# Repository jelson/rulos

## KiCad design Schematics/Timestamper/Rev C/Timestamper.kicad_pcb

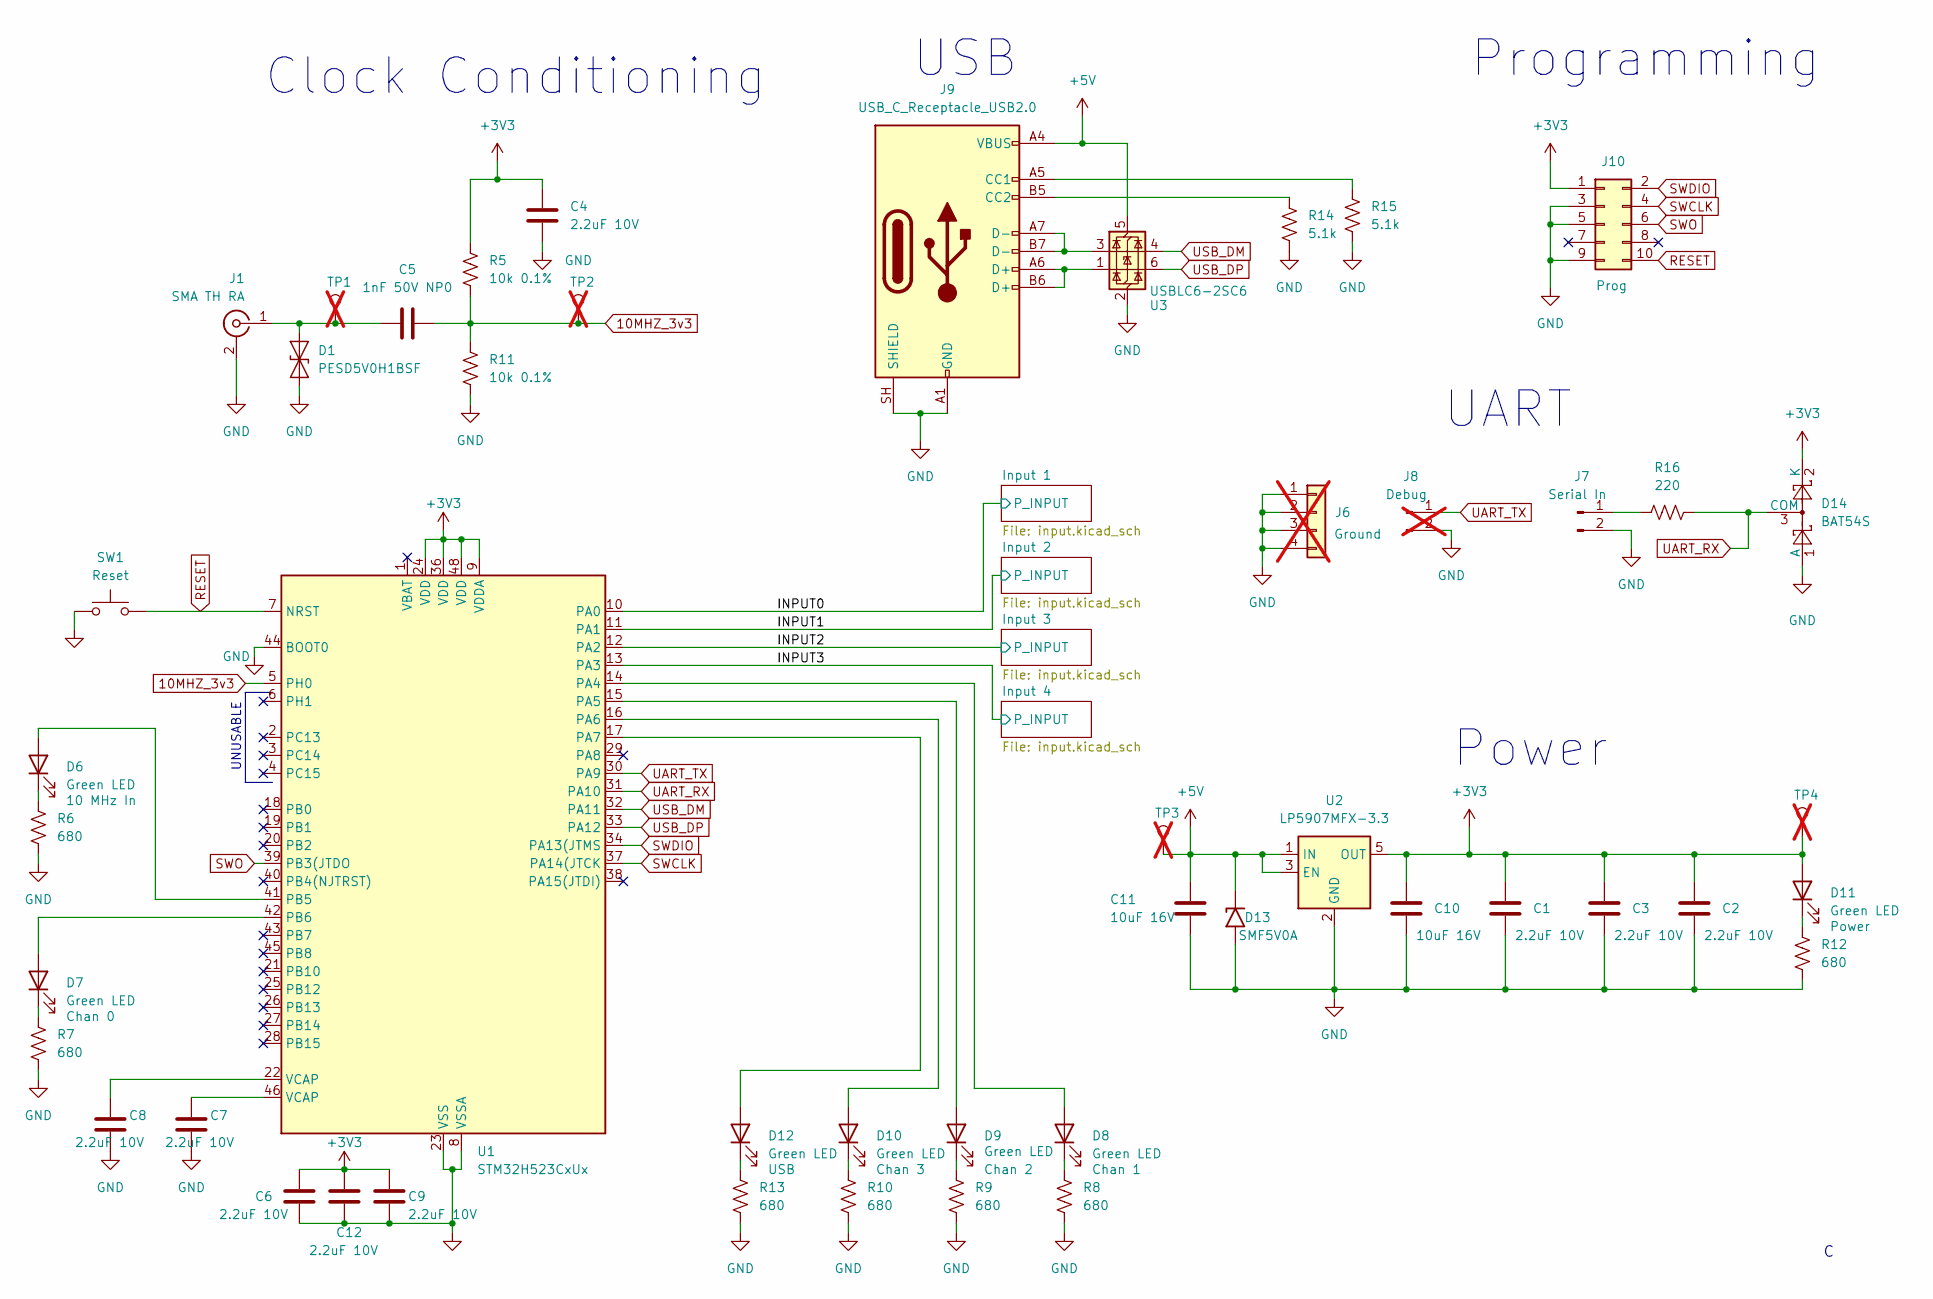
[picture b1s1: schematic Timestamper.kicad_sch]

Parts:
C1, C2, C3, C4, C6, C7, C8, C9, C12: 2.2uF 10V; C_0603_1608Metric_Pad1.08x0.95mm_HandSolder
C5: 1nF 50V NP0; C_0603_1608Metric_Pad1.08x0.95mm_HandSolder
C10, C11: 10uF 16V; C_0805_2012Metric_Pad1.18x1.45mm_HandSolder
D1: PESD5V0H1BSF; Nexperia_DSN0603-2_0.6x0.3mm_P0.4mm
D6, D7, D8, D9, D10, D11, D12: Green LED; LED_0603_1608Metric_Pad1.05x0.95mm_HandSolder
D13: SMF5V0A; D_SOD-123F
D14: BAT54S; SOT-23
J1: SMA TH RA; LINX_CONSMA002-G
J6: 0.1" Header; PinHeader_1x04_P2.54mm_Vertical; not fitted
J7: 0.1" Header; PinHeader_1x02_P2.54mm_Vertical
J8: 0.1" Header; PinHeader_1x02_P2.54mm_Vertical; not fitted
J9: USB_C_Receptacle_USB2.0; USB_C_Receptacle_HRO_TYPE-C-31-M-12
J10: 0.05" 5x2; ARM_CORTEX_PROGHDR_SMT
R5, R11: 10k 0.1%; R_0603_1608Metric_Pad0.98x0.95mm_HandSolder
R6, R7, R8, R9, R10, R12, R13: 680; R_0603_1608Metric_Pad0.98x0.95mm_HandSolder
R14, R15: 5.1k; R_0603_1608Metric_Pad0.98x0.95mm_HandSolder
R16: 220; R_1206_3216Metric_Pad1.30x1.75mm_HandSolder
SW1: Tact buton; SW_Push_1P1T_NO_E-Switch_TL3301NxxxxxG
TP1, TP2, TP3, TP4: TestPoint; TestPoint_THTPad_D2.0mm_Drill1.0mm; not fitted
U1: STM32H523CxUx; QFN-48-1EP_7x7mm_P0.5mm_EP5.6x5.6mm
U2: LP5907MFX-3.3; SOT-23-5
U3: USBLC6-2SC6; SOT-23-6

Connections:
10MHZ_3v3: C5.2, R5.1, R11.2, TP2.1 (1_1), U1.5 (PH0)
+3V3: C1.1, C2.1, C3.1, C4.1, C6.2, C9.2, C10.2, C12.2, D11.2 (A), D14.2 (K), J10.1, R5.2, TP4.1 (1_1), U1.9 (VDDA), U1.24 (VDD), U1.36 (VDD), U1.48 (VDD), U2.5 (OUT); also elsewhere on the board
+5V: C11.2, D13.1 (A1), J9.A4 (VBUS), J9.A9 (VBUS), J9.B4 (VBUS), J9.B9 (VBUS), TP3.1 (1_1), U2.1 (IN), U2.3 (EN), U3.5 (VBUS)
/INPUT0: U1.10 (PA0); also elsewhere on the board
/INPUT1: U1.11 (PA1); also elsewhere on the board
/INPUT2: U1.12 (PA2); also elsewhere on the board
/INPUT3: U1.13 (PA3); also elsewhere on the board
GND: C1.2, C2.2, C3.2, C4.2, C6.1, C7.1, C8.1, C9.1, C10.1, C11.1, C12.1, D1.1 (A1), D13.2 (A2), D14.1 (A), J1.2 (Ext), J6.1, J6.2, J6.3, J6.4, J7.2, J8.2, J9.A1 (GND), J9.A12 (GND), J9.B1 (GND), J9.B12 (GND), J9.SH (SHIELD), J10.3, J10.5, J10.9, R6.2, R7.2, R8.2, R9.2, R10.2, R11.1, R12.2, R13.2, R14.2, R15.2, SW1.1, U1.8 (VSSA), U1.23 (VSS), U1.35 (VSS), U1.44 (BOOT0), U1.47 (VSS), U1.49 (VSS), U2.2 (GND), U3.2 (GND); also elsewhere on the board
unnamed: C7.2, U1.46 (VCAP)
unnamed: C8.2, U1.22 (VCAP)
unnamed: C5.1, D1.2 (A2), J1.1 (In), TP1.1 (1_1)
unnamed: D6.2 (A), U1.41 (PB5)
unnamed: D6.1 (K), R6.1
unnamed: D7.2 (A), U1.42 (PB6)
unnamed: D7.1 (K), R7.1
unnamed: D8.2 (A), U1.14 (PA4)
unnamed: D8.1 (K), R8.1
unnamed: D9.2 (A), U1.15 (PA5)
unnamed: D9.1 (K), R9.1
unnamed: D10.2 (A), U1.16 (PA6)
unnamed: D10.1 (K), R10.1
unnamed: D11.1 (K), R12.1
unnamed: D12.2 (A), U1.17 (PA7)
unnamed: D12.1 (K), R13.1
unnamed: J7.1, R16.1
unnamed: J9.A5 (CC1), R15.1
unnamed: J9.B5 (CC2), R14.1
unnamed: J9.A6 (D+), J9.B6 (D+), U3.1 (I/O2)
unnamed: J9.A7 (D-), J9.B7 (D-), U3.3 (I/O1)
RESET: J10.10, SW1.2, U1.7 (NRST)
SWCLK: J10.4, U1.37 (PA14(JTCK)
SWDIO: J10.2, U1.34 (PA13(JTMS)
SWO: J10.6, U1.39 (PB3(JTDO)
UART_RX: D14.3 (COM), R16.2, U1.31 (PA10)
UART_TX: J8.1, U1.30 (PA9)
USB_DM: U1.32 (PA11), U3.4 (I/O1)
USB_DP: U1.33 (PA12), U3.6 (I/O2)

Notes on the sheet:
USB
Programming
UNUSABLE
Clock Conditioning
UART
Power

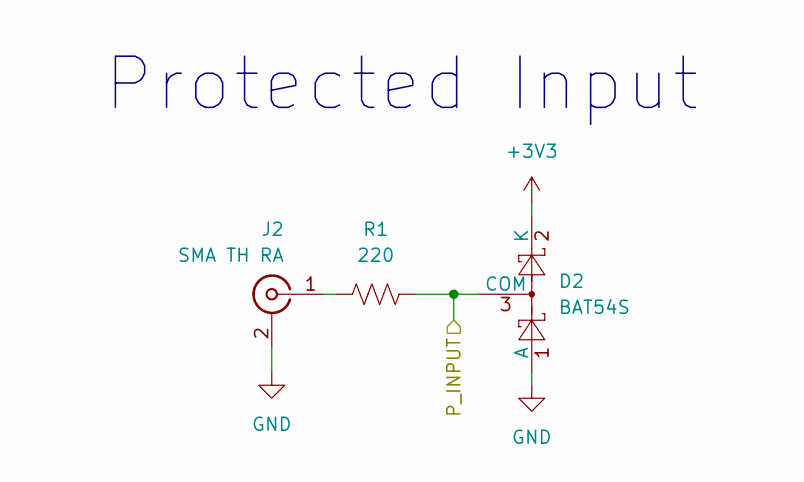
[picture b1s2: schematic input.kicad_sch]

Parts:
D2: BAT54S; SOT-23
J2: SMA TH RA; LINX_CONSMA002-G
R1: 220; R_1206_3216Metric_Pad1.30x1.75mm_HandSolder

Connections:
+3V3: D2.2 (K); also elsewhere on the board
/INPUT0: D2.3 (COM), R1.2; also elsewhere on the board
GND: D2.1 (A), J2.2 (Ext); also elsewhere on the board
unnamed: J2.1 (In), R1.1

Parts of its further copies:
D3, D4, D5: BAT54S; SOT-23
J3, J4, J5: SMA TH RA; LINX_CONSMA002-G
R2, R3, R4: 220; R_1206_3216Metric_Pad1.30x1.75mm_HandSolder

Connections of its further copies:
+3V3: D3.2 (K), D4.2 (K), D5.2 (K); also elsewhere on the board
/INPUT1: D3.3 (COM), R2.2; also elsewhere on the board
/INPUT2: D4.3 (COM), R3.2; also elsewhere on the board
/INPUT3: D5.3 (COM), R4.2; also elsewhere on the board
GND: D3.1 (A), D4.1 (A), D5.1 (A), J3.2 (Ext), J4.2 (Ext), J5.2 (Ext); also elsewhere on the board
unnamed: J3.1 (In), R2.1
unnamed: J4.1 (In), R3.1
unnamed: J5.1 (In), R4.1

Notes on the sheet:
Protected Input

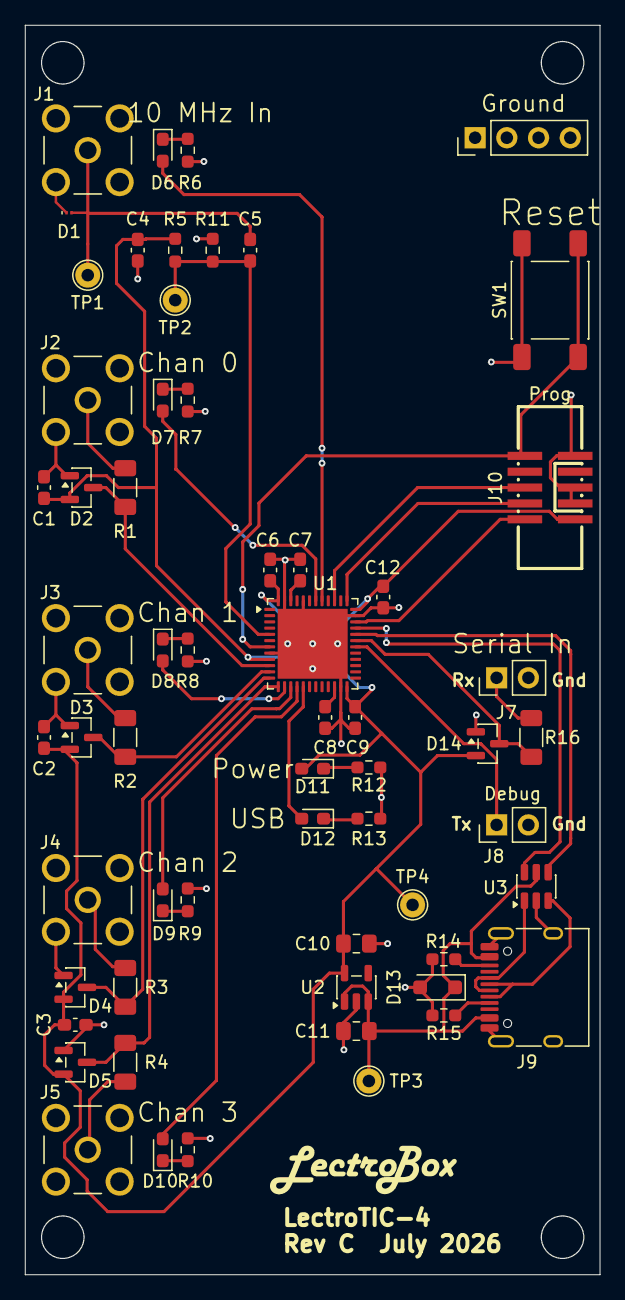
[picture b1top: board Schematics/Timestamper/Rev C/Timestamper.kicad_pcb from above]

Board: 2 copper layers, 46.0 x 100.0 mm, 60 parts (0 on the bottom side), 41 nets.

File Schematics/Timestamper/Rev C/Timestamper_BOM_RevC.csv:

"Reference","Value","Footprint","Qty","DNP","Link"
"C1,C2,C3,C4,C6,C7,C8,C9,C12","2.2uF 10V","Capacitor_SMD:C_0603_1608Metric_Pad1.08x0.95mm_HandSolder","9","","https://www.lcsc.com/product-detail/C100082.html"
"C5","1nF 50V NP0","Capacitor_SMD:C_0603_1608Metric_Pad1.08x0.95mm_HandSolder","1","","https://www.lcsc.com/product-detail/C106246.html"
"C10,C11","10uF 16V","Capacitor_SMD:C_0805_2012Metric_Pad1.18x1.45mm_HandSolder","2","","https://www.lcsc.com/product-detail/C95841.html"
"D1","PESD5V0H1BSF","Diode_SMD:Nexperia_DSN0603-2_0.6x0.3mm_P0.4mm","1","","https://www.lcsc.com/product-detail/C478002.html"
"D2,D3,D4,D5,D14","BAT54S","Package_TO_SOT_SMD:SOT-23","5","","https://www.lcsc.com/product-detail/C19726.html"
"D6,D7,D8,D9,D10,D11,D12","Green LED","LED_SMD:LED_0603_1608Metric_Pad1.05x0.95mm_HandSolder","7","","https://www.lcsc.com/product-detail/C125094.html"
"D13","SMF5V0A","Diode_SMD:D_SOD-123F","1","","https://www.lcsc.com/product-detail/C151296.html"
"J1,J2,J3,J4,J5","SMA TH RA","Lectrobox:LINX_CONSMA002-G","5","","https://www.lcsc.com/product-detail/C496551.html"
"J6,J7","0.1"" Header","Connector_PinHeader_2.54mm:PinHeader_1x02_P2.54mm_Vertical,Connector_PinHeader_2.54mm:PinHeader_1x04_P2.54mm_Vertical","2","","https://www.lcsc.com/product-detail/C160332.html"
"J8","0.1"" Header","Connector_PinHeader_2.54mm:PinHeader_1x02_P2.54mm_Vertical","1","DNP",""
"J9","USB_C_Receptacle_USB2.0","Connector_USB:USB_C_Receptacle_HRO_TYPE-C-31-M-12","1","","https://www.lcsc.com/product-detail/C165948.html"
"J10","0.05"" 5x2","Lectrobox:ARM_CORTEX_PROGHDR_SMT","1","","https://www.lcsc.com/product-detail/C42372555.html"
"R1,R2,R3,R4,R16","220","Resistor_SMD:R_1206_3216Metric_Pad1.30x1.75mm_HandSolder","5","","https://www.lcsc.com/product-detail/C2078575.html"
"R5,R11","10k 0.1%","Resistor_SMD:R_0603_1608Metric_Pad0.98x0.95mm_HandSolder","2","","https://www.lcsc.com/product-detail/C844890.html"
"R6,R7,R8,R9,R10,R12,R13","680","Resistor_SMD:R_0603_1608Metric_Pad0.98x0.95mm_HandSolder","7","","https://www.lcsc.com/product-detail/C2907062.html"
"R14,R15","5.1k","Resistor_SMD:R_0603_1608Metric_Pad0.98x0.95mm_HandSolder","2","","https://www.lcsc.com/product-detail/C2907044.html"
"SW1","Tact buton","Button_Switch_SMD:SW_Push_1P1T_NO_E-Switch_TL3301NxxxxxG","1","","https://www.lcsc.com/product-detail/C381039.html"
"TP1,TP2,TP3,TP4","TestPoint","TestPoint:TestPoint_THTPad_D2.0mm_Drill1.0mm","4","DNP",""
"U1","STM32H523CxUx","Package_DFN_QFN:QFN-48-1EP_7x7mm_P0.5mm_EP5.6x5.6mm","1","","https://www.lcsc.com/product-detail/C26082147.html, or https://www.verical.com/pd/stmicroelectronics-microcontrolle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, or https://www.digikey.cn/zh/products/detail/stmicroelectronics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"
"U2","LP5907MFX-3.3","Package_TO_SOT_SMD:SOT-23-5","1","","https://www.lcsc.com/product-detail/C80670.html"
"U3","USBLC6-2SC6","Package_TO_SOT_SMD:SOT-23-6","1","","https://www.lcsc.com/product-detail/C7519.html"

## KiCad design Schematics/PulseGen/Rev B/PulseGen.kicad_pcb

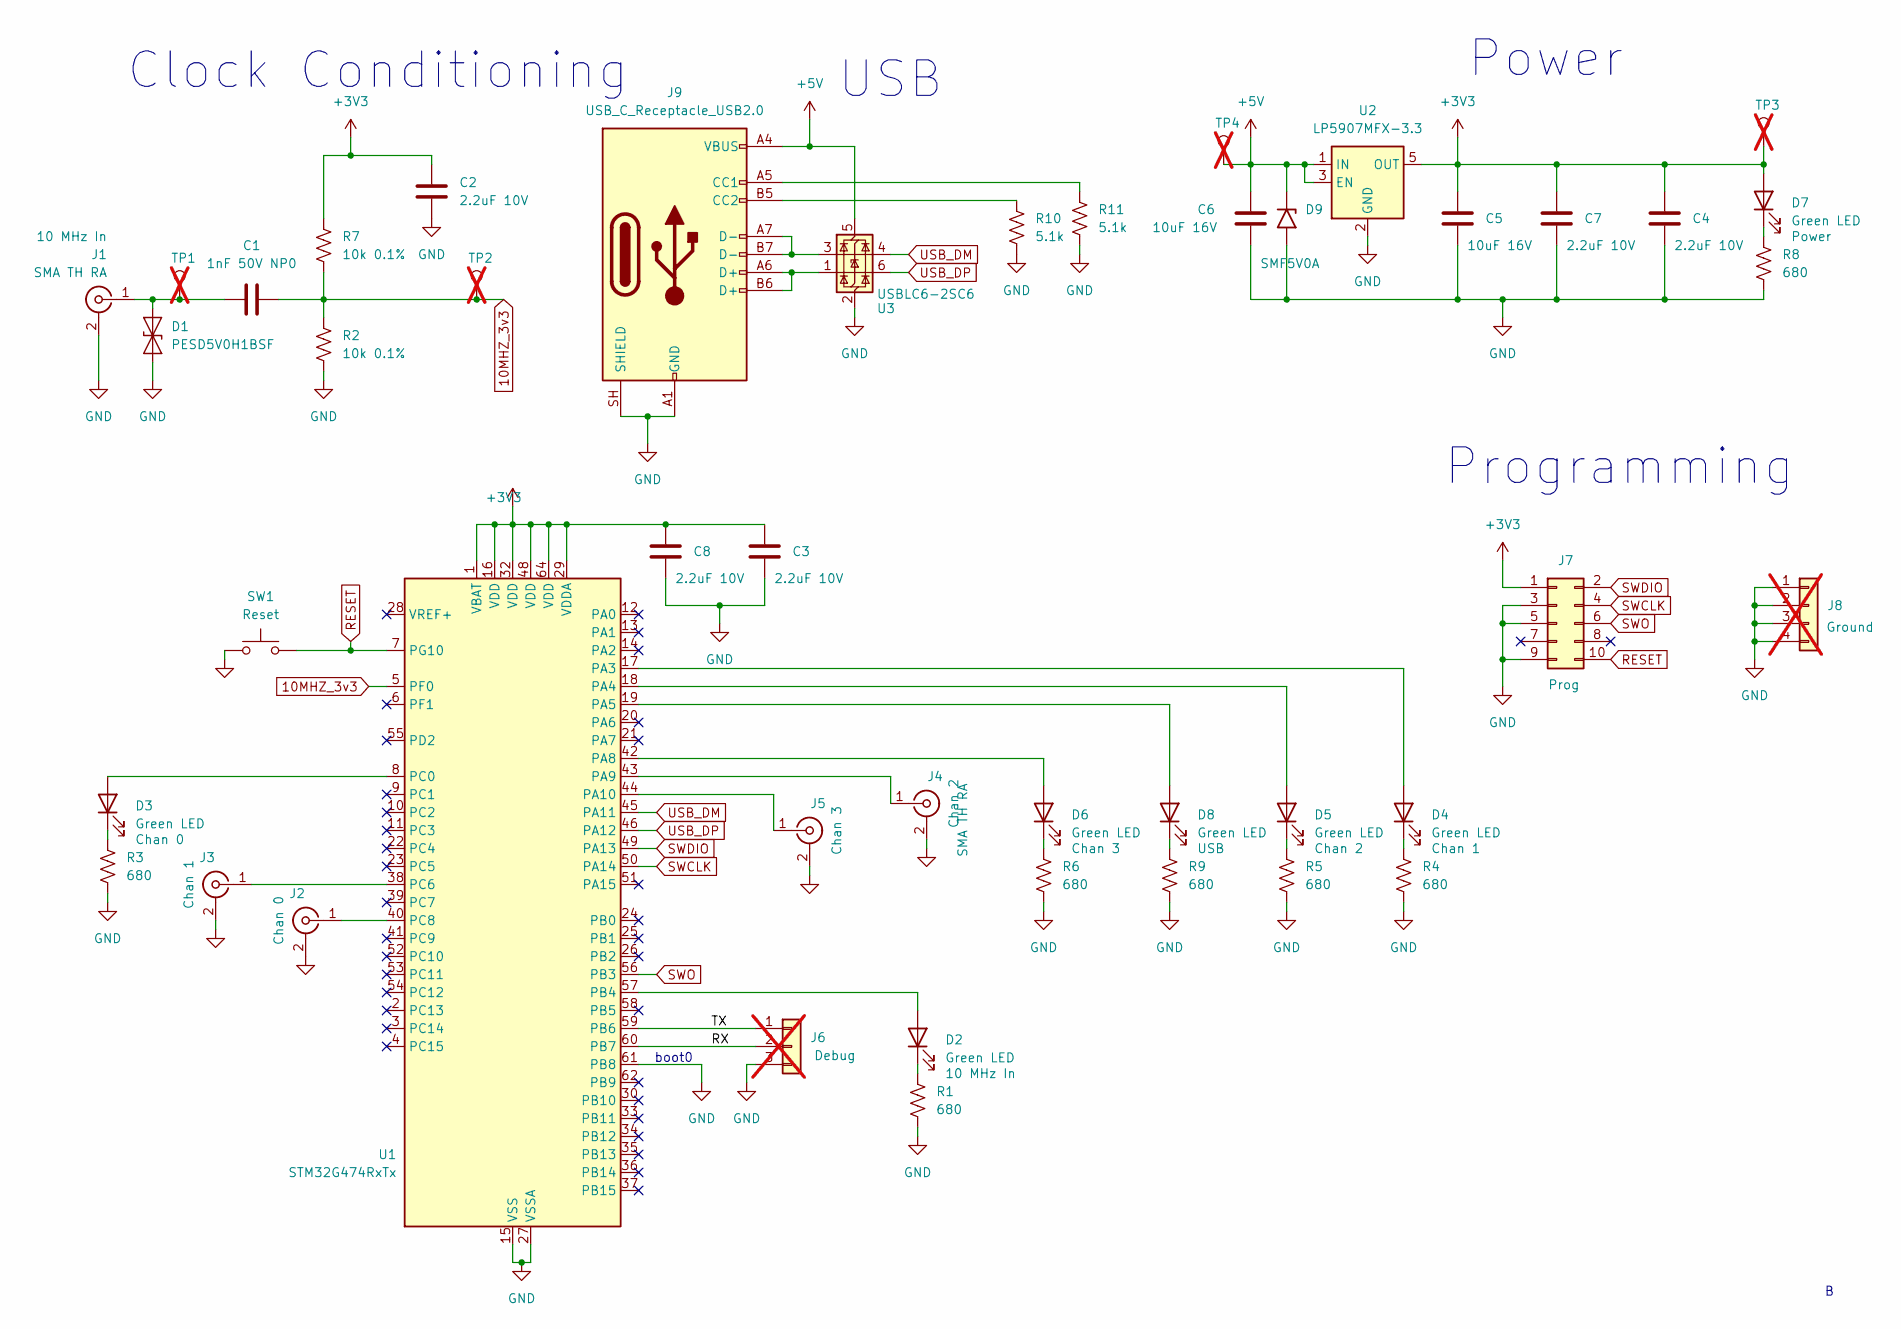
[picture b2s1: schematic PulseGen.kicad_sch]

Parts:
C1: 1nF 50V NP0; C_0603_1608Metric_Pad1.08x0.95mm_HandSolder
C2, C3, C4, C7, C8: 2.2uF 10V; C_0603_1608Metric_Pad1.08x0.95mm_HandSolder
C5, C6: 10uF 16V; C_0805_2012Metric_Pad1.18x1.45mm_HandSolder
D1: PESD5V0H1BSF; Nexperia_DSN0603-2_0.6x0.3mm_P0.4mm
D2, D3, D4, D5, D6, D7, D8: Green LED; LED_0603_1608Metric_Pad1.05x0.95mm_HandSolder
D9: SMF5V0A; D_SOD-123F
J1, J2, J3, J4, J5: SMA TH RA; LINX_CONSMA002-G
J6: 0.1" Header; PinHeader_1x03_P2.54mm_Vertical; not fitted
J7: 0.05" 5x2; ARM_CORTEX_PROGHDR_SMT
J8: 0.1" Header; PinHeader_1x04_P2.54mm_Vertical; not fitted
J9: USB_C_Receptacle_USB2.0; USB_C_Receptacle_HRO_TYPE-C-31-M-12
R1, R3, R4, R5, R6, R8, R9: 680; R_0603_1608Metric_Pad0.98x0.95mm_HandSolder
R2, R7: 10k 0.1%; R_0603_1608Metric_Pad0.98x0.95mm_HandSolder
R10, R11: 5.1k; R_0603_1608Metric_Pad0.98x0.95mm_HandSolder
SW1: Tact buton; SW_Push_1P1T_NO_E-Switch_TL3301NxxxxxG
TP1, TP2, TP3, TP4: TestPoint; TestPoint_THTPad_D2.0mm_Drill1.0mm; not fitted
U1: STM32G474RxTx; LQFP-64_10x10mm_P0.5mm
U2: LP5907MFX-3.3; SOT-23-5
U3: USBLC6-2SC6; SOT-23-6

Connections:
10MHZ_3v3: C1.2, R2.2, R7.1, TP2.1 (1_1), U1.5 (PF0)
+3V3: C2.1, C3.1, C4.1, C5.2, C7.1, C8.1, D7.2 (A), J7.1, R7.2, TP3.1 (1_1), U1.1 (VBAT), U1.16 (VDD), U1.29 (VDDA), U1.32 (VDD), U1.48 (VDD), U1.64 (VDD), U2.5 (OUT)
+5V: C6.2, D9.1 (A1), J9.A4 (VBUS), J9.A9 (VBUS), J9.B4 (VBUS), J9.B9 (VBUS), TP4.1 (1_1), U2.1 (IN), U2.3 (EN), U3.5 (VBUS)
/RX: J6.2, U1.60 (PB7)
/TX: J6.1, U1.59 (PB6)
GND: C2.2, C3.2, C4.2, C5.1, C6.1, C7.2, C8.2, D1.1 (A1), D9.2 (A2), J1.2 (Ext), J2.2 (Ext), J3.2 (Ext), J4.2 (Ext), J5.2 (Ext), J6.3, J7.3, J7.5, J7.9, J8.1, J8.2, J8.3, J8.4, J9.A1 (GND), J9.A12 (GND), J9.B1 (GND), J9.B12 (GND), J9.SH (SHIELD), R1.2, R2.1, R3.2, R4.2, R5.2, R6.2, R8.2, R9.2, R10.2, R11.2, SW1.1, U1.15 (VSS), U1.27 (VSSA), U1.31 (VSS), U1.47 (VSS), U1.61 (PB8), U1.63 (VSS), U2.2 (GND), U3.2 (GND)
unnamed: C1.1, D1.2 (A2), J1.1 (In), TP1.1 (1_1)
unnamed: D2.2 (A), U1.57 (PB4)
unnamed: D2.1 (K), R1.1
unnamed: D3.2 (A), U1.8 (PC0)
unnamed: D3.1 (K), R3.1
unnamed: D4.2 (A), U1.17 (PA3)
unnamed: D4.1 (K), R4.1
unnamed: D5.2 (A), U1.18 (PA4)
unnamed: D5.1 (K), R5.1
unnamed: D6.2 (A), U1.42 (PA8)
unnamed: D6.1 (K), R6.1
unnamed: D7.1 (K), R8.1
unnamed: D8.2 (A), U1.19 (PA5)
unnamed: D8.1 (K), R9.1
unnamed: J2.1 (In), U1.40 (PC8)
unnamed: J3.1 (In), U1.38 (PC6)
unnamed: J4.1 (In), U1.43 (PA9)
unnamed: J5.1 (In), U1.44 (PA10)
unnamed: J9.A5 (CC1), R11.1
unnamed: J9.B5 (CC2), R10.1
unnamed: J9.A6 (D+), J9.B6 (D+), U3.1 (I/O2)
unnamed: J9.A7 (D-), J9.B7 (D-), U3.3 (I/O1)
RESET: J7.10, SW1.2, U1.7 (PG10)
SWCLK: J7.4, U1.50 (PA14)
SWDIO: J7.2, U1.49 (PA13)
SWO: J7.6, U1.56 (PB3)
USB_DM: U1.45 (PA11), U3.4 (I/O1)
USB_DP: U1.46 (PA12), U3.6 (I/O2)

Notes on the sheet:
USB
Power
Clock Conditioning
Programming
boot0

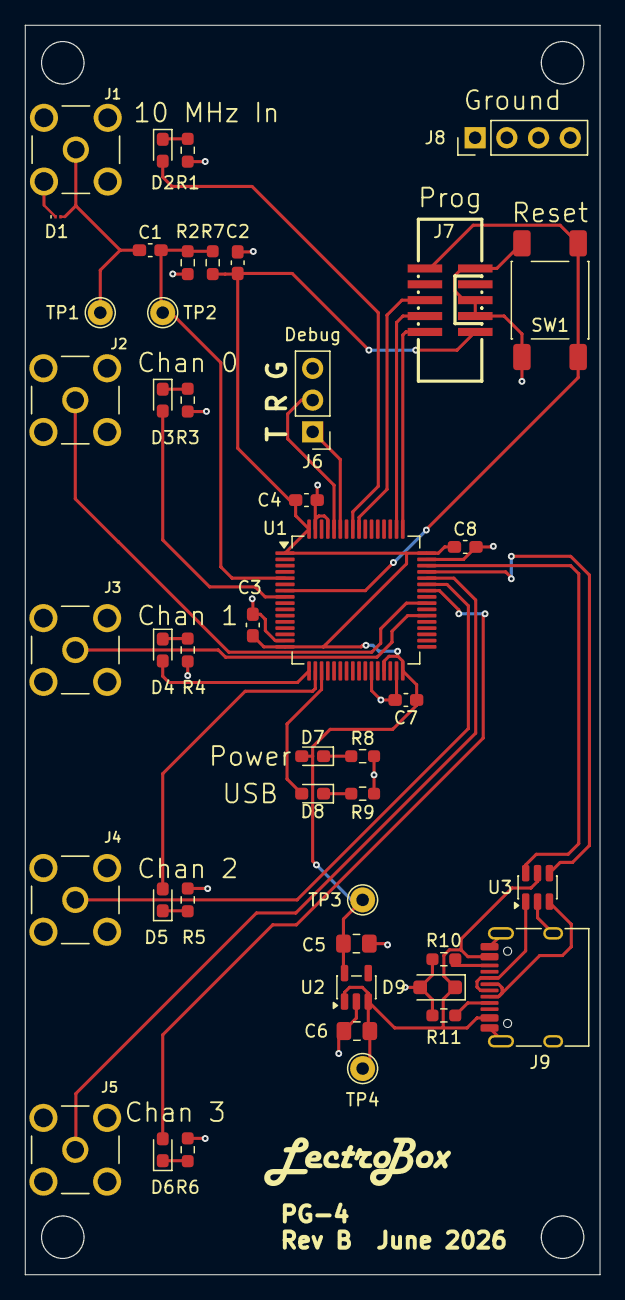
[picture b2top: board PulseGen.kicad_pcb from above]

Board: 2 copper layers, 46.0 x 100.0 mm, 45 parts (0 on the bottom side), 34 nets.

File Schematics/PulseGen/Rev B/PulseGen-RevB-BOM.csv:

"Reference","Qty","Value","DNP","Footprint","Link"
"C1","1","1nF 50V NP0","","Capacitor_SMD:C_0603_1608Metric_Pad1.08x0.95mm_HandSolder","https://www.lcsc.com/product-detail/C106246.html"
"C2,C3,C4,C7,C8","5","2.2uF 10V","","Capacitor_SMD:C_0603_1608Metric_Pad1.08x0.95mm_HandSolder","https://www.lcsc.com/product-detail/C100082.html"
"C5,C6","2","10uF 16V","","Capacitor_SMD:C_0805_2012Metric_Pad1.18x1.45mm_HandSolder","https://www.lcsc.com/product-detail/C95841.html"
"D1","1","PESD5V0H1BSF","","Diode_SMD:Nexperia_DSN0603-2_0.6x0.3mm_P0.4mm","https://www.lcsc.com/product-detail/C478002.html"
"D2,D3,D4,D5,D6,D7,D8","7","Green LED","","LED_SMD:LED_0603_1608Metric_Pad1.05x0.95mm_HandSolder","https://www.lcsc.com/product-detail/C125094.html"
"D9","1","SMF5V0A","","Diode_SMD:D_SOD-123F","https://www.lcsc.com/product-detail/C151296.html"
"J1,J2,J3,J4,J5","5","SMA TH RA","","Lectrobox:LINX_CONSMA002-G","https://www.lcsc.com/product-detail/C496551.html"
"J6","1","0.1"" Header","DNP","Connector_PinHeader_2.54mm:PinHeader_1x03_P2.54mm_Vertical",""
"J7","1","0.05"" 5x2","","Lectrobox:ARM_CORTEX_PROGHDR_SMT","https://www.lcsc.com/product-detail/C42372555.html"
"J8","1","0.1"" Header","DNP","Connector_PinHeader_2.54mm:PinHeader_1x04_P2.54mm_Vertical",""
"J9","1","USB_C_Receptacle_USB2.0","","Connector_USB:USB_C_Receptacle_HRO_TYPE-C-31-M-12","https://www.lcsc.com/product-detail/C165948.html"
"R1,R3,R4,R5,R6,R8,R9","7","680","","Resistor_SMD:R_0603_1608Metric_Pad0.98x0.95mm_HandSolder","https://www.lcsc.com/product-detail/C2907062.html"
"R2,R7","2","10k 0.1%","","Resistor_SMD:R_0603_1608Metric_Pad0.98x0.95mm_HandSolder","https://www.lcsc.com/product-detail/C190610.html"
"R10,R11","2","5.1k","","Resistor_SMD:R_0603_1608Metric_Pad0.98x0.95mm_HandSolder","https://www.lcsc.com/product-detail/C125891.html"
"SW1","1","Tact buton","","Button_Switch_SMD:SW_Push_1P1T_NO_E-Switch_TL3301NxxxxxG","https://www.lcsc.com/product-detail/C381039.html"
"TP1,TP2,TP3,TP4","4","TestPoint","DNP","TestPoint:TestPoint_THTPad_D2.0mm_Drill1.0mm",""
"U1","1","STM32G474RxTx","","Package_QFP:LQFP-64_10x10mm_P0.5mm","https://www.lcsc.com/product-detail/C529413.html"
"U2","1","LP5907MFX-3.3","","Package_TO_SOT_SMD:SOT-23-5","https://www.lcsc.com/product-detail/C80670.html"
"U3","1","USBLC6-2SC6","","Package_TO_SOT_SMD:SOT-23-6","https://www.lcsc.com/product-detail/C7519.html"

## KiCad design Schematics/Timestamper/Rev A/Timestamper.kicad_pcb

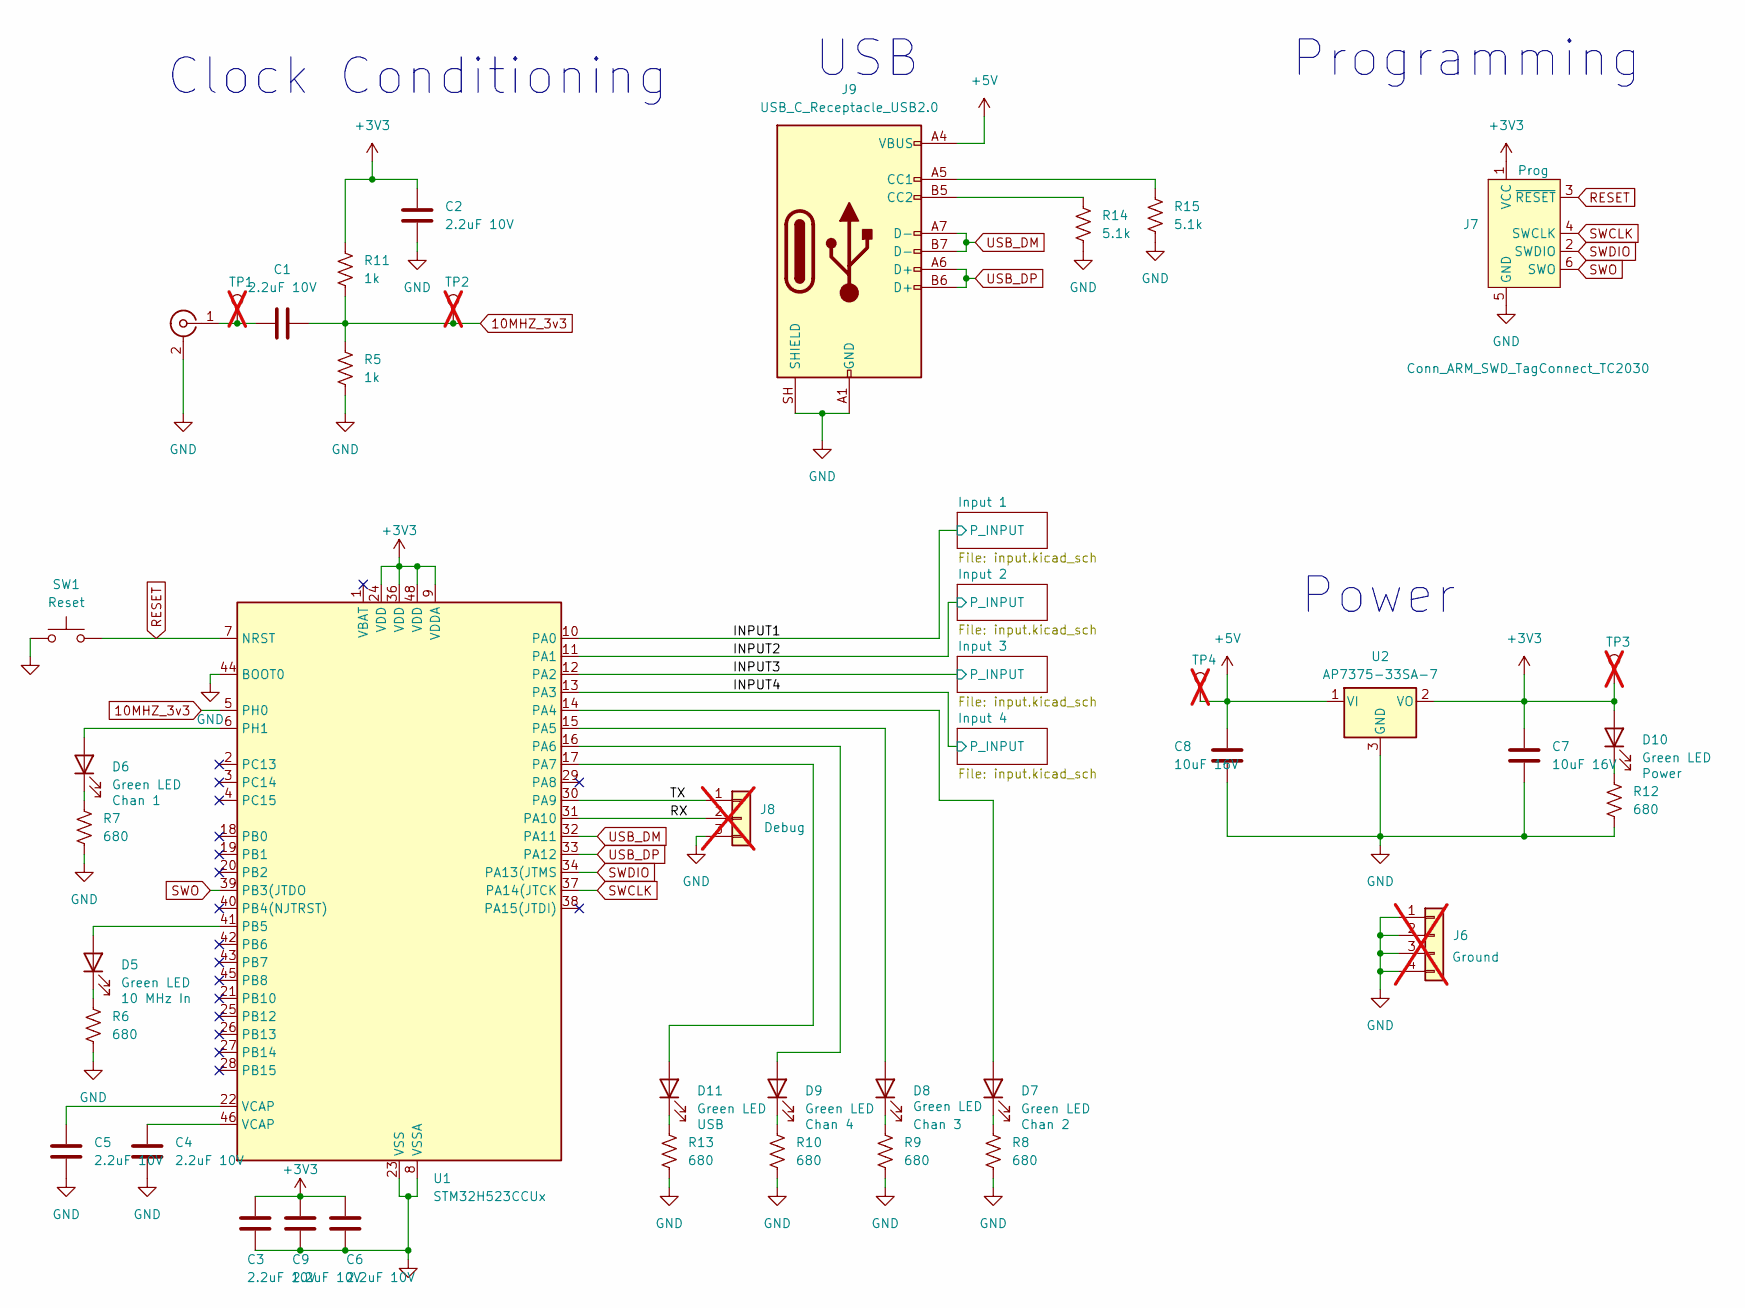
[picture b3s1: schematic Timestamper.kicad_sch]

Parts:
C1, C2, C3, C4, C5, C6, C9: 2.2uF 10V; C_0603_1608Metric_Pad1.08x0.95mm_HandSolder
C7, C8: 10uF 16V; C_0805_2012Metric_Pad1.18x1.45mm_HandSolder
D5, D6, D7, D8, D9, D10, D11: Green LED; LED_0603_1608Metric_Pad1.05x0.95mm_HandSolder
J1: SMA TH RA; LINX_CONSMA002-G
J6: 0.1" Header; PinHeader_1x04_P2.54mm_Vertical; not fitted
J7: Conn_ARM_SWD_TagConnect_TC2030; Tag-Connect_TC2030-IDC-FP_2x03_P1.27mm_Vertical
J8: 0.1" Header; PinHeader_1x03_P2.54mm_Vertical; not fitted
J9: USB_C_Receptacle_USB2.0; USB_C_Receptacle_HRO_TYPE-C-31-M-12
R5, R11: 1k; R_0603_1608Metric_Pad0.98x0.95mm_HandSolder
R6, R7, R8, R9, R10, R12, R13: 680; R_0603_1608Metric_Pad0.98x0.95mm_HandSolder
R14, R15: 5.1k; R_0603_1608Metric_Pad0.98x0.95mm_HandSolder
SW1: Tact buton; SW_Push_1P1T_NO_E-Switch_TL3301NxxxxxG
TP1, TP2, TP3, TP4: TestPoint; TestPoint_THTPad_D2.0mm_Drill1.0mm; not fitted
U1: STM32H523CCUx; QFN-48-1EP_7x7mm_P0.5mm_EP5.6x5.6mm
U2: AP7375-33SA-7; SOT-23

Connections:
10MHZ_3v3: C1.2, R5.2, R11.1, TP2.1 (1_1), U1.5 (PH0)
+3V3: C2.1, C3.2, C6.2, C7.2, C9.2, D10.2 (A), J7.1 (VCC), R11.2, TP3.1 (1_1), U1.9 (VDDA), U1.24 (VDD), U1.36 (VDD), U1.48 (VDD), U2.2 (VO); also elsewhere on the board
+5V: C8.2, J9.A4 (VBUS), J9.A9 (VBUS), J9.B4 (VBUS), J9.B9 (VBUS), TP4.1 (1_1), U2.1 (VI)
/INPUT1: U1.10 (PA0); also elsewhere on the board
/INPUT2: U1.11 (PA1); also elsewhere on the board
/INPUT3: U1.12 (PA2); also elsewhere on the board
/INPUT4: U1.13 (PA3); also elsewhere on the board
/RX: J8.2, U1.31 (PA10)
/TX: J8.1, U1.30 (PA9)
GND: C2.2, C3.1, C4.1, C5.1, C6.1, C7.1, C8.1, C9.1, J1.2 (Ext), J6.1, J6.2, J6.3, J6.4, J7.5 (GND), J8.3, J9.A1 (GND), J9.A12 (GND), J9.B1 (GND), J9.B12 (GND), J9.SH (SHIELD), R5.1, R6.2, R7.2, R8.2, R9.2, R10.2, R12.2, R13.2, R14.2, R15.2, SW1.1, U1.8 (VSSA), U1.23 (VSS), U1.35 (VSS), U1.44 (BOOT0), U1.47 (VSS), U1.49 (VSS), U2.3 (GND); also elsewhere on the board
unnamed: C4.2, U1.46 (VCAP)
unnamed: C5.2, U1.22 (VCAP)
unnamed: D5.2 (A), U1.41 (PB5)
unnamed: D5.1 (K), R6.1
unnamed: D6.2 (A), U1.6 (PH1)
unnamed: D6.1 (K), R7.1
unnamed: D7.2 (A), U1.14 (PA4)
unnamed: D7.1 (K), R8.1
unnamed: D8.2 (A), U1.15 (PA5)
unnamed: D8.1 (K), R9.1
unnamed: D9.2 (A), U1.16 (PA6)
unnamed: D9.1 (K), R10.1
unnamed: D10.1 (K), R12.1
unnamed: D11.2 (A), U1.17 (PA7)
unnamed: D11.1 (K), R13.1
unnamed: C1.1, J1.1 (In), TP1.1 (1_1)
unnamed: J9.A5 (CC1), R15.1
unnamed: J9.B5 (CC2), R14.1
RESET: J7.3 (~RESET), SW1.2, U1.7 (NRST)
SWCLK: J7.4 (SWCLK), U1.37 (PA14(JTCK)
SWDIO: J7.2 (SWDIO), U1.34 (PA13(JTMS)
SWO: J7.6 (SWO), U1.39 (PB3(JTDO)
USB_DM: J9.A7 (D-), J9.B7 (D-), U1.32 (PA11)
USB_DP: J9.A6 (D+), J9.B6 (D+), U1.33 (PA12)

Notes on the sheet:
USB
Programming
Clock Conditioning
Power

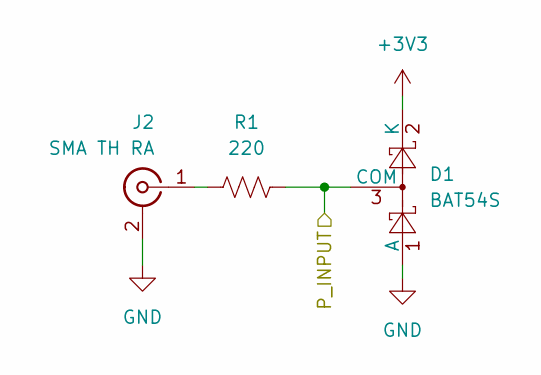
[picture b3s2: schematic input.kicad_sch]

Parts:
D1: BAT54S; SOT-23
J2: SMA TH RA; LINX_CONSMA002-G
R1: 220; R_0603_1608Metric_Pad0.98x0.95mm_HandSolder

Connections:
+3V3: D1.2 (K); also elsewhere on the board
/INPUT1: D1.3 (COM), R1.2; also elsewhere on the board
GND: D1.1 (A), J2.2 (Ext); also elsewhere on the board
unnamed: J2.1 (In), R1.1

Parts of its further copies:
D2, D3, D4: BAT54S; SOT-23
J3, J4, J5: SMA TH RA; LINX_CONSMA002-G
R2, R3, R4: 220; R_0603_1608Metric_Pad0.98x0.95mm_HandSolder

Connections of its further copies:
+3V3: D2.2 (K), D3.2 (K), D4.2 (K); also elsewhere on the board
/INPUT2: D2.3 (COM), R2.2; also elsewhere on the board
/INPUT3: D3.3 (COM), R3.2; also elsewhere on the board
/INPUT4: D4.3 (COM), R4.2; also elsewhere on the board
GND: D2.1 (A), D3.1 (A), D4.1 (A), J3.2 (Ext), J4.2 (Ext), J5.2 (Ext); also elsewhere on the board
unnamed: J3.1 (In), R2.1
unnamed: J4.1 (In), R3.1
unnamed: J5.1 (In), R4.1

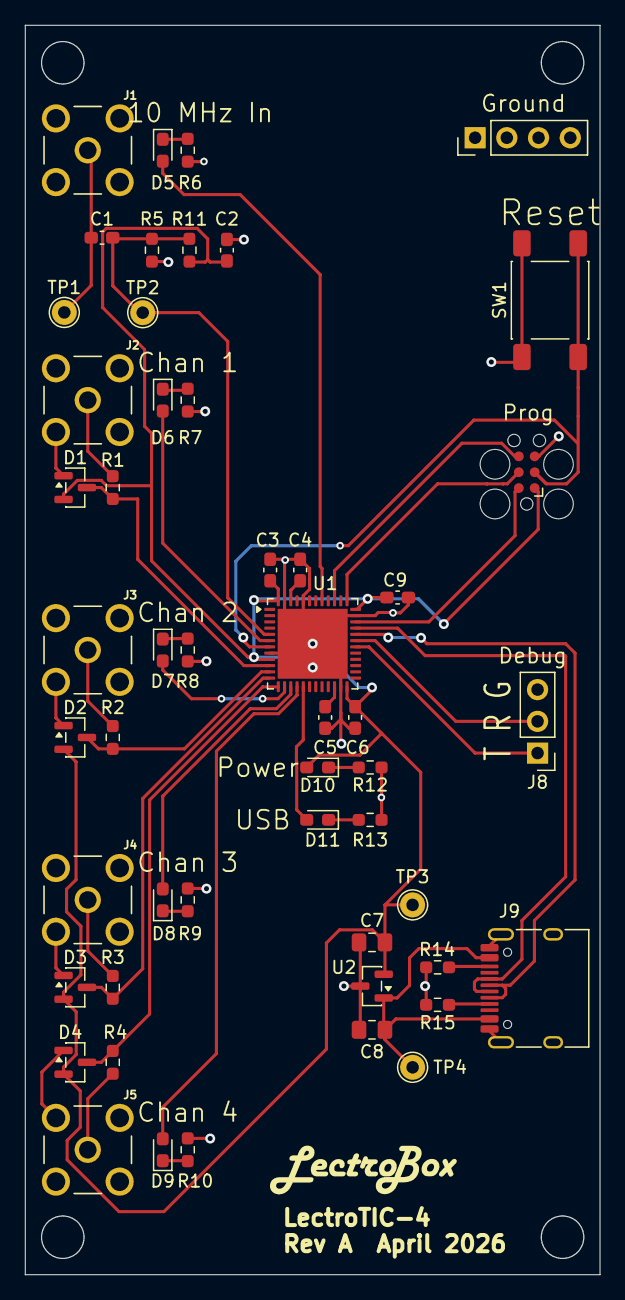
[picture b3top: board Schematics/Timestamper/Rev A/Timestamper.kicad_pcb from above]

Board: 2 copper layers, 46.0 x 100.0 mm, 51 parts (0 on the bottom side), 38 nets.

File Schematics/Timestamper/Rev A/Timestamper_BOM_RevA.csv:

"Reference","Value","Footprint","Qty","DNP","User Label","Link"
"C1,C2,C3,C4,C5,C6,C9","2.2uF 10V","Capacitor_SMD:C_0603_1608Metric_Pad1.08x0.95mm_HandSolder","7","","","https://www.lcsc.com/product-detail/C100082.html"
"C7,C8","10uF 16V","Capacitor_SMD:C_0805_2012Metric_Pad1.18x1.45mm_HandSolder","2","","","https://www.lcsc.com/product-detail/C95841.html"
"D1,D2,D3,D4","BAT54S","Package_TO_SOT_SMD:SOT-23","4","","","https://www.lcsc.com/product-detail/C19726.html"
"D5,D6,D7,D8,D9,D10,D11","Green LED","LED_SMD:LED_0603_1608Metric_Pad1.05x0.95mm_HandSolder","7","","10 MHz In,Chan 1,Chan 2,Chan 3,Chan 4,Power,USB","https://www.lcsc.com/product-detail/C125094.html"
"J1,J2,J3,J4,J5","SMA TH RA","Lectrobox:LINX_CONSMA002-G","5","","","https://www.lcsc.com/product-detail/C496551.html"
"J6,J8","0.1"" Header","Connector_PinHeader_2.54mm:PinHeader_1x03_P2.54mm_Vertical,Connector_PinHeader_2.54mm:PinHeader_1x04_P2.54mm_Vertical","2","DNP","Debug,Ground",""
"J9","USB_C_Receptacle_USB2.0","Connector_USB:USB_C_Receptacle_HRO_TYPE-C-31-M-12","1","","","https://www.lcsc.com/product-detail/C165948.html"
"R1,R2,R3,R4","220","Resistor_SMD:R_0603_1608Metric_Pad0.98x0.95mm_HandSolder","4","","","https://www.lcsc.com/product-detail/C107696.html"
"R5,R11","1k","Resistor_SMD:R_0603_1608Metric_Pad0.98x0.95mm_HandSolder","2","","","https://www.lcsc.com/product-detail/C22548.html"
"R6,R7,R8,R9,R10,R12,R13","680","Resistor_SMD:R_0603_1608Metric_Pad0.98x0.95mm_HandSolder","7","","","https://www.lcsc.com/product-detail/C112310.html"
"R14,R15","5.1k","Resistor_SMD:R_0603_1608Metric_Pad0.98x0.95mm_HandSolder","2","","","https://www.lcsc.com/product-detail/C105580.html"
"SW1","Tact buton","Button_Switch_SMD:SW_Push_1P1T_NO_E-Switch_TL3301NxxxxxG","1","","Reset","https://www.lcsc.com/product-detail/C381039.html"
"TP1,TP2,TP3,TP4","TestPoint","TestPoint:TestPoint_THTPad_D2.0mm_Drill1.0mm","4","DNP","",""
"U1","STM32H523CCUx","Package_DFN_QFN:QFN-48-1EP_7x7mm_P0.5mm_EP5.6x5.6mm","1","","","https://www.lcsc.com/product-detail/C23898421.html"
"U2","AP7375-33SA-7","Package_TO_SOT_SMD:SOT-23","1","","","https://www.lcsc.com/product-detail/C5944186.html"
